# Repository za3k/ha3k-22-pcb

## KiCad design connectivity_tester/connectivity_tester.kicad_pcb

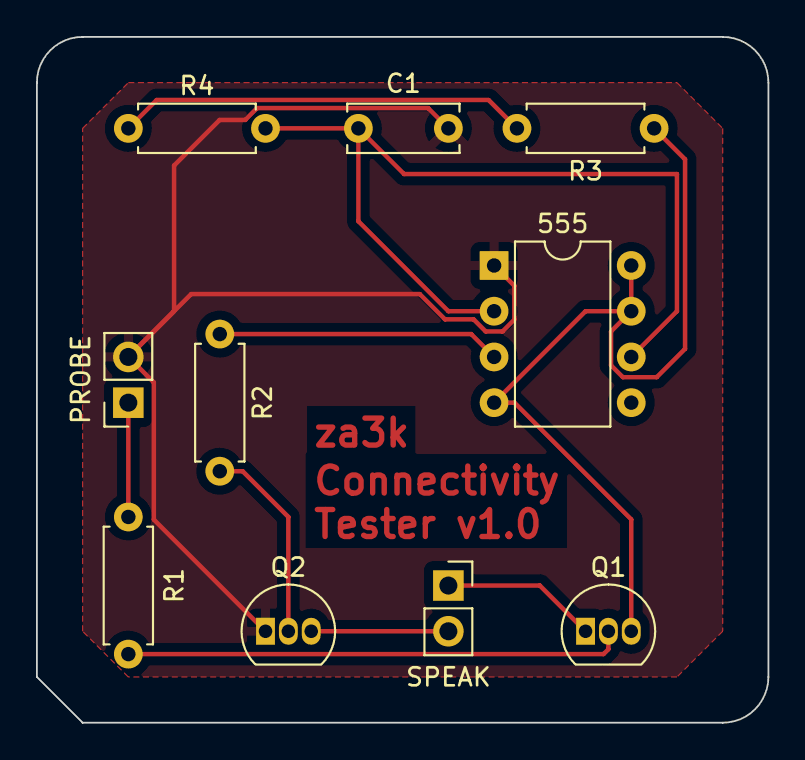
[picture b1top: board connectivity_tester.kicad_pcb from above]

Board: 2 copper layers, 40.6 x 38.1 mm, 10 parts (0 on the bottom side), 10 nets.

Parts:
555: DIP-8_W7.62mm
C1: 100nF; C_Disc_D6.0mm_W2.5mm_P5.00mm
PROBE: Probes; PinSocket_1x02_P2.54mm_Vertical
Q1: 2N3906; TO-92_Inline
Q2: 2N3904; TO-92_Inline
R1: 1k; R_Axial_DIN0207_L6.3mm_D2.5mm_P7.62mm_Horizontal
R2, R3: 100; R_Axial_DIN0207_L6.3mm_D2.5mm_P7.62mm_Horizontal
R4: 10k; R_Axial_DIN0207_L6.3mm_D2.5mm_P7.62mm_Horizontal
SPEAK: Speaker; PinSocket_1x02_P2.54mm_Vertical

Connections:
+9V: Q1.1 (E), SPEAK.1
GND: 555.1 (GND), C1.2, PROBE.2, Q2.1 (E)
unnamed: PROBE.1, R1.2
unnamed: Q1.2 (B), R1.1
unnamed: 555.4 (RESET), 555.7 (DISCH), 555.8 (Vcc), Q1.3 (C), R3.1
unnamed: Q2.2 (B), R2.2
unnamed: Q2.3 (C), SPEAK.2
unnamed: R3.2, R4.1
unnamed: 555.3 (OUT), R2.1
unnamed: 555.2 (TRIG), 555.6 (THRES), C1.1, R4.2

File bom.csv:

Part Number,Part Name,Description,Quantity,Unit of Measure,Procurement Type,References
1.00,CF14JT100R,"100 ohm resistor, through-hole",1.00,each,Off the shelf,"R2, R3"
2.00,CF14JT1K00 ,"1k ohm resistor, through-hole",1.00,each,Off the shelf,R1
3.00,CF14JT10K0,"10k ohm resistor, through-hole",1.00,each,Off the shelf,R4
4.00,HEAD2,"2-pin header socket, 2.54mm spacing",1.00,each,Off the shelf,"SPEAK, PROBE"
5.00,2N3906,"PNP Transistor, through-hole",1.00,each,Off the shelf,Q1
6.00,2N3904,"NPN Transistor, through-hole",1.00,each,Off the shelf,Q2
7.00,296-NE555P-ND,"NE555 timer, 2.54mm DIP",1.00,each,Off the shelf,555
8.00,C100nF,"100nF capacitor, ceramic disc, through-hole",1.00,each,Off the shelf,C1
